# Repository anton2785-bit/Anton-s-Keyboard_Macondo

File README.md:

# Anton's kayboard
--- 
### What is this project
* This is a keyboar that uses thr 1800 compact layout (an almost 100% keyboard without most of the keys between the enter and the numpad). This keyboard uses an rp2040 chip for its 30 gpio pins that make the making of the keyboard PCB layout easier. Bellow every hotswapable key there is a LED that is wired to every other one and can be controlled with code. 

--- 
### Why I made this project
* I made this keyboard because I wanted to try a bigger more complx PCB that I would be able to use everyday.
* Also I wanted to update my keyboard with one that I made.

--- 
### Images
* The schematic for the PCB

* The schematic for the hierarchal sheets and what is in it

* The layout and the PCB

* The 3D model of the case and assembly of the keyboard
* 

--- 
### BOM
| Component | Purpose | Qty | Total Cost (USD) | Distributor |
|-----------|---------|:---:|:----------------:|-------------|
| Gateron Stabilizer | Prevents larger switches from wobbling | 1 | $9.45 | Gateron |
| Decoupling Capacitors (100nF) | Reduce electrical noise before the LEDs | 2 | $3.20 | AliExpress |
| LEDs (SK6812 Mini-E) | RGB underglow beneath the switches | 1 | $3.56 | AliExpress |
| Keycaps | Keycaps | 1 | $15.78 | AliExpress |
| Rotary Encoder (EC11E) | Rotary knob for volume / scroll | 1 | $2.78 | AliExpress |
| Diodes (1N4148W) | Prevent signal backflow in the matrix | 2 | $3.60 | AliExpress |
| Resistors (4.7 kΩ and 350 Ω) | Current limiting for LEDs and I²C pull-ups | 1 | $4.10 | AliExpress |
| Foam | Sound dampening layer under the PCB | 1 | $7.77 | AliExpress |
| Coiled Cable | Connecting cable for the keyboard | 1 | $5.55 | AliExpress |
| PCB | Main circuit board | 1 | $59.00 | JLCPCB |
| Microcontroller (YD-RP2040) | Runs the keyboard firmware (KMK / CircuitPython) | 1 | $2.94 | AliExpress |
| Gateron Switches | The switches you type on | 1 | $29.00 | Gateron |
| Hotswap Sockets | Allow switches to be swapped without soldering | 1 | $6.68 | Gateron |
| **Total** | | | **$153.51** | |

--- 
### Assembly
* First you need to soulder the smaller components (the diodes and capacitors) just for your sanity because later it will get harder.
* The secpnd smallest thingyou need to soulder many of are the LEDs.
* After that you are free to soulder the hotswap sockets.
* The chip can be souldered at any time.
* The keys and kaycaps must be placed after the PCB is put into the case and secured with the top case.

--- 
### Known problems
* The code is almost entirely made by claude because I dont have the chip with me and I cant write the code.

--- 
### Credits
* Designed and built by *(Anton/ Anton-2785-bit)
* Inspired by open‑source mechanical keyboard and hackpad communities (https://forge.hackclub.com/).

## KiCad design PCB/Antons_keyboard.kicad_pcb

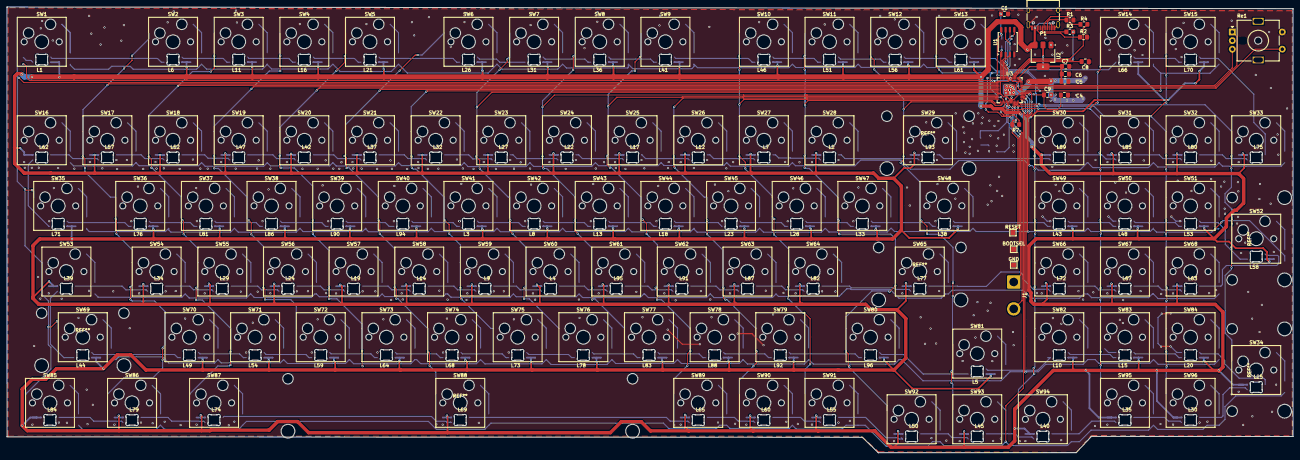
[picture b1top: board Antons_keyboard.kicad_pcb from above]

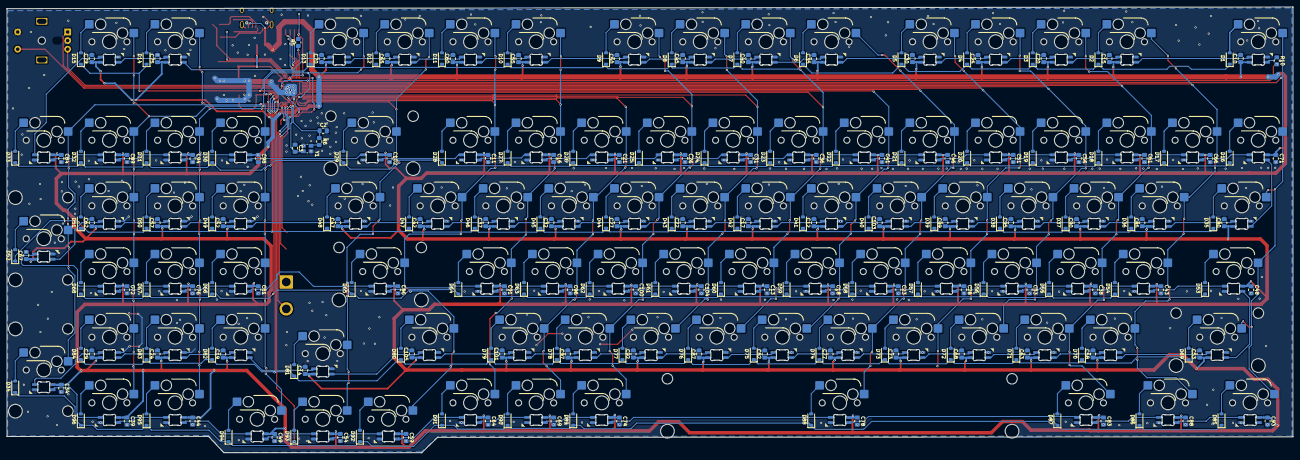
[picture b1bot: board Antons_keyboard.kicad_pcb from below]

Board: 2 copper layers, 373.2 x 129.3 mm, 411 parts (198 on the bottom side), 241 nets.

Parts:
BOOTSEL: TestPoint; TestPoint_Pad_1.5x1.5mm
C1, C4, C5, C6, C7, C9: 100nF; C_0805_2012Metric_Pad1.18x1.45mm_HandSolder
C2, C3: 27pF; C_0805_2012Metric_Pad1.18x1.45mm_HandSolder
C8: 1uF; C_0805_2012Metric_Pad1.18x1.45mm_HandSolder
C10, C11, C12, C13, C14, C15, C16, C17, C18, C19, C20, C21, C22, C23, C24, C25, C26, C27, C28, C29, C30, C31, C32, C33, C34, C35, C36, C37, C38, C39, C40, C41, C42, C43, C44, C45, C46, C47, C48, C49, C50, C51, C52, C53, C54, C55, C56, C57, C58, C59, C60, C61, C62, C63, C64, C65, C66, C67, C68, C69, C70, C71, C72, C73, C74, C75, C76, C77, C78, C79, C80, C81, C82, C83, C84, C85, C86, C87, C88, C89, C90, C91, C92, C93, C94, C95, C96, C97, C98, C99, C100, C101, C102, C103, C104, C105: C; C_0805_2012Metric_Pad1.18x1.45mm_HandSolder
D1, D2, D3, D4, D5, D6, D7, D8, D9, D10, D11, D12, D13, D14, D15, D16, D17, D18, D19, D20, D21, D22, D23, D24, D25, D26, D27, D28, D29, D30, D31, D32, D33, D34, D35, D36, D37, D38, D39, D40, D41, D42, D43, D44, D45, D46, D47, D48, D49, D50, D51, D52, D53, D54, D55, D56, D57, D58, D59, D60, D61, D62, D63, D64, D65, D66, D67, D68, D69, D70, D71, D72, D73, D74, D75, D76, D77, D78, D79, D80, D81, D82, D83, D84, D85, D86, D87, D88, D89, D90, D91, D92, D93, D94, D95, D96: 1N4148W; D_SOD-123
GND: TestPoint; TestPoint_Pad_1.5x1.5mm
J1: debug pins; SolderWire-2sqmm_1x02_P7.8mm_D2mm_OD3.9mm
L1, L2, L3, L4, L5, L6, L7, L8, L9, L10, L11, L12, L13, L14, L15, L16, L17, L18, L19, L20, L21, L22, L23, L24, L25, L26, L27, L28, L29, L30, L31, L32, L33, L34, L35, L36, L37, L38, L39, L40, L41, L42, L43, L44, L45, L46, L47, L48, L49, L50, L51, L52, L53, L54, L55, L56, L57, L58, L59, L60, L61, L62, L63, L64, L65, L66, L67, L68, L69, L70, L71, L72, L73, L74, L75, L76, L77, L78, L79, L80, L81, L82, L83, L84, L85, L86, L87, L88, L89, L90, L91, L92, L93, L94, L95, L96: SK6812MINI-E; SK6812MINI-E_fixed
P1: USB_C_Plug_USB2.0; USB_C_Receptacle_HRO_TYPE-C-31-M-12
R1, R2: 5.1kΩ; R_0805_2012Metric_Pad1.20x1.40mm_HandSolder
R3, R4: 27Ω; R_0805_2012Metric_Pad1.20x1.40mm_HandSolder
R5, R7: 10k; R_0805_2012Metric_Pad1.20x1.40mm_HandSolder
R6: 1k; R_0805_2012Metric_Pad1.20x1.40mm_HandSolder
R10: 470; R_0805_2012Metric_Pad1.20x1.40mm_HandSolder
RESET: TestPoint; TestPoint_Pad_1.5x1.5mm
Re1: RotaryEncoder_Switch; RotaryEncoder_Alps_EC11E-Switch_Vertical_H20mm_MountingHoles
SW1, SW2, SW3, SW4, SW5, SW6, SW7, SW8, SW9, SW10, SW11, SW12, SW13, SW14, SW15, SW16, SW17, SW18, SW19, SW20, SW21, SW22, SW23, SW24, SW25, SW26, SW27, SW28, SW30, SW31, SW32, SW33, SW36, SW37, SW38, SW39, SW40, SW41, SW42, SW43, SW44, SW45, SW46, SW47, SW49, SW50, SW51, SW54, SW55, SW56, SW57, SW58, SW59, SW60, SW61, SW62, SW63, SW64, SW66, SW67, SW68, SW70, SW71, SW72, SW73, SW74, SW75, SW76, SW77, SW78, SW79, SW80, SW81, SW82, SW83, SW84, SW89, SW90, SW91, SW92, SW93, SW94, SW95, SW96: SW_Push; Hotswap_MX_1.00u
SW29: SW_Push; Hotswap_MX_2.00u
SW34, SW52: SW_Push; Hotswap_MX_2.00u_90deg
SW35, SW48: SW_Push; Hotswap_MX_1.50u
SW53: SW_Push; Hotswap_MX_1.75u
SW65, SW69: SW_Push; Hotswap_MX_2.25u
SW85, SW86, SW87: SW_Push; Hotswap_MX_1.25u
SW88: SW_Push; Hotswap_MX_6.25u
U1: W25Q32JVSS; SOIC-8_5.3x5.3mm_P1.27mm
U2: AMS1117-3.3; SOT-223-3_TabPin2
U3: RP2040; QFN-56-1EP_7x7mm_P0.4mm_EP3.2x3.2mm
Y1: TSX-3225_12.0000MF18X-C; XTAL_TSX-3225_24.0000MF18X-C

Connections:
+3.3V: C1.1, C4.1, C5.1, C6.1, C7.1, C9.1, R5.2, R7.1, U1.8 (VCC), U2.2 (VO), U3.1 (IOVDD), U3.10 (IOVDD), U3.22 (IOVDD), U3.23 (DVDD), U3.33 (IOVDD), U3.42 (IOVDD), U3.43 (ADC_AVDD), U3.44 (VREG_VIN), U3.48 (USB_VDD), U3.49 (IOVDD), U3.50 (DVDD)
+5V: C10.1, C11.1, C12.1, C13.1, C14.1, C15.1, C16.1, C17.1, C18.1, C19.1, C20.1, C21.1, C22.1, C23.1, C24.1, C25.1, C26.1, C27.1, C28.1, C29.1, C30.1, C31.1, C32.1, C33.1, C34.1, C35.1, C36.1, C37.1, C38.1, C39.1, C40.1, C41.1, C42.1, C43.1, C44.1, C45.1, C46.1, C47.1, C48.1, C49.1, C50.1, C51.1, C52.1, C53.1, C54.1, C55.1, C56.1, C57.1, C58.1, C59.1, C60.1, C61.1, C62.1, C63.1, C64.1, C65.1, C66.1, C67.1, C68.1, C69.1, C70.1, C71.1, C72.1, C73.1, C74.1, C75.1, C76.1, C77.1, C78.1, C79.1, C80.1, C81.1, C82.1, C83.1, C84.1, C85.1, C86.1, C87.1, C88.1, C89.1, C90.1, C91.1, C92.1, C93.1, C94.1, C95.1, C96.1, C97.1, C98.1, C99.1, C100.1, C101.1, C102.1, C103.1, C104.1, C105.1, L1.1 (VDD), L2.1 (VDD), L3.1 (VDD), L4.1 (VDD), L5.1 (VDD), L6.1 (VDD), L7.1 (VDD), L8.1 (VDD), L9.1 (VDD), L10.1 (VDD), L11.1 (VDD), L12.1 (VDD), L13.1 (VDD), L14.1 (VDD), L15.1 (VDD), L16.1 (VDD), L17.1 (VDD), L18.1 (VDD), L19.1 (VDD), L20.1 (VDD), L21.1 (VDD), L22.1 (VDD), L23.1 (VDD), L24.1 (VDD), L25.1 (VDD), L26.1 (VDD), L27.1 (VDD), L28.1 (VDD), L29.1 (VDD), L30.1 (VDD), L31.1 (VDD), L32.1 (VDD), L33.1 (VDD), L34.1 (VDD), L35.1 (VDD), L36.1 (VDD), L37.1 (VDD), L38.1 (VDD), L39.1 (VDD), L40.1 (VDD), L41.1 (VDD), L42.1 (VDD), L43.1 (VDD), L44.1 (VDD), L45.1 (VDD), L46.1 (VDD), L47.1 (VDD), L48.1 (VDD), L49.1 (VDD), L50.1 (VDD), L51.1 (VDD), L52.1 (VDD), L53.1 (VDD), L54.1 (VDD), L55.1 (VDD), L56.1 (VDD), L57.1 (VDD), L58.1 (VDD), L59.1 (VDD), L60.1 (VDD), L61.1 (VDD), L62.1 (VDD), L63.1 (VDD), L64.1 (VDD), L65.1 (VDD), L66.1 (VDD), L67.1 (VDD), L68.1 (VDD), L69.1 (VDD), L70.1 (VDD), L71.1 (VDD), L72.1 (VDD), L73.1 (VDD), L74.1 (VDD), L75.1 (VDD), L76.1 (VDD), L77.1 (VDD), L78.1 (VDD), L79.1 (VDD), L80.1 (VDD), L81.1 (VDD), L82.1 (VDD), L83.1 (VDD), L84.1 (VDD), L85.1 (VDD), L86.1 (VDD), L87.1 (VDD), L88.1 (VDD), L89.1 (VDD), L90.1 (VDD), L91.1 (VDD), L92.1 (VDD), L93.1 (VDD), L94.1 (VDD), L95.1 (VDD), L96.1 (VDD), P1.A4 (VBUS), P1.A9 (VBUS), P1.B4 (VBUS), P1.B9 (VBUS), U2.3 (VI)
DATA LED: R10.2, U3.36 (GPIO24)
GND: C1.2, C2.2, C3.1, C4.2, C5.2, C6.2, C7.2, C8.1, C9.2, C10.2, C11.2, C12.2, C13.2, C14.2, C15.2, C16.2, C17.2, C18.2, C19.2, C20.2, C21.2, C22.2, C23.2, C24.2, C25.2, C26.2, C27.2, C28.2, C29.2, C30.2, C31.2, C32.2, C33.2, C34.2, C35.2, C36.2, C37.2, C38.2, C39.2, C40.2, C41.2, C42.2, C43.2, C44.2, C45.2, C46.2, C47.2, C48.2, C49.2, C50.2, C51.2, C52.2, C53.2, C54.2, C55.2, C56.2, C57.2, C58.2, C59.2, C60.2, C61.2, C62.2, C63.2, C64.2, C65.2, C66.2, C67.2, C68.2, C69.2, C70.2, C71.2, C72.2, C73.2, C74.2, C75.2, C76.2, C77.2, C78.2, C79.2, C80.2, C81.2, C82.2, C83.2, C84.2, C85.2, C86.2, C87.2, C88.2, C89.2, C90.2, C91.2, C92.2, C93.2, C94.2, C95.2, C96.2, C97.2, C98.2, C99.2, C100.2, C101.2, C102.2, C103.2, C104.2, C105.2, GND.1 (1_1), L1.3 (VSS), L2.3 (VSS), L3.3 (VSS), L4.3 (VSS), L5.3 (VSS), L6.3 (VSS), L7.3 (VSS), L8.3 (VSS), L9.3 (VSS), L10.3 (VSS), L11.3 (VSS), L12.3 (VSS), L13.3 (VSS), L14.3 (VSS), L15.3 (VSS), L16.3 (VSS), L17.3 (VSS), L18.3 (VSS), L19.3 (VSS), L20.3 (VSS), L21.3 (VSS), L22.3 (VSS), L23.3 (VSS), L24.3 (VSS), L25.3 (VSS), L26.3 (VSS), L27.3 (VSS), L28.3 (VSS), L29.3 (VSS), L30.3 (VSS), L31.3 (VSS), L32.3 (VSS), L33.3 (VSS), L34.3 (VSS), L35.3 (VSS), L36.3 (VSS), L37.3 (VSS), L38.3 (VSS), L39.3 (VSS), L40.3 (VSS), L41.3 (VSS), L42.3 (VSS), L43.3 (VSS), L44.3 (VSS), L45.3 (VSS), L46.3 (VSS), L47.3 (VSS), L48.3 (VSS), L49.3 (VSS), L50.3 (VSS), L51.3 (VSS), L52.3 (VSS), L53.3 (VSS), L54.3 (VSS), L55.3 (VSS), L56.3 (VSS), L57.3 (VSS), L58.3 (VSS), L59.3 (VSS), L60.3 (VSS), L61.3 (VSS), L62.3 (VSS), L63.3 (VSS), L64.3 (VSS), L65.3 (VSS), L66.3 (VSS), L67.3 (VSS), L68.3 (VSS), L69.3 (VSS), L70.3 (VSS), L71.3 (VSS), L72.3 (VSS), L73.3 (VSS), L74.3 (VSS), L75.3 (VSS), L76.3 (VSS), L77.3 (VSS), L78.3 (VSS), L79.3 (VSS), L80.3 (VSS), L81.3 (VSS), L82.3 (VSS), L83.3 (VSS), L84.3 (VSS), L85.3 (VSS), L86.3 (VSS), L87.3 (VSS), L88.3 (VSS), L89.3 (VSS), L90.3 (VSS), L91.3 (VSS), L92.3 (VSS), L93.3 (VSS), L94.3 (VSS), L95.3 (VSS), L96.3 (VSS), P1.A1 (GND), P1.A12 (GND), P1.B1 (GND), P1.B12 (GND), P1.SH (SHIELD), R1.2, R2.2, Re1.C, Re1.S2, U1.4 (GND), U2.1 (GND), U3.19 (TESTEN), U3.57 (GND), Y1.2 (GND), Y1.4 (GND)
unnamed: D1.2 (A), SW1.2
unnamed: D2.2 (A), SW2.2
unnamed: D3.2 (A), SW3.2
unnamed: D4.2 (A), SW4.2
unnamed: D5.2 (A), SW5.2
unnamed: D6.2 (A), SW6.2
unnamed: D7.2 (A), SW7.2
unnamed: D8.2 (A), SW8.2
unnamed: D9.2 (A), SW9.2
unnamed: D10.2 (A), SW10.2
unnamed: D11.2 (A), SW11.2
unnamed: D12.2 (A), SW12.2
unnamed: D13.2 (A), SW13.2
unnamed: D14.2 (A), SW14.2
unnamed: D15.2 (A), SW15.2
unnamed: D16.2 (A), SW16.2
unnamed: D17.2 (A), SW17.2
unnamed: D18.2 (A), SW18.2
unnamed: D19.2 (A), SW19.2
unnamed: D20.2 (A), SW20.2
unnamed: D21.2 (A), SW21.2
unnamed: D22.2 (A), SW22.2
unnamed: D23.2 (A), SW23.2
unnamed: D24.2 (A), SW24.2
unnamed: D25.2 (A), SW25.2
unnamed: D26.2 (A), SW26.2
unnamed: D27.2 (A), SW27.2
unnamed: D28.2 (A), SW28.2
unnamed: D29.2 (A), SW29.2
unnamed: D30.2 (A), SW30.2
unnamed: D31.2 (A), SW31.2
unnamed: D32.2 (A), SW32.2
unnamed: D33.2 (A), SW33.2
unnamed: D34.2 (A), SW34.2
unnamed: D35.2 (A), SW35.2
unnamed: D36.2 (A), SW36.2
unnamed: D37.2 (A), SW37.2
unnamed: D38.2 (A), SW38.2
unnamed: D39.2 (A), SW39.2
unnamed: D40.2 (A), SW40.2
unnamed: D41.2 (A), SW41.2
unnamed: D42.2 (A), SW42.2
unnamed: D43.2 (A), SW43.2
unnamed: D44.2 (A), SW44.2
unnamed: D45.2 (A), SW45.2
unnamed: D46.2 (A), SW46.2
unnamed: D47.2 (A), SW47.2
unnamed: D48.2 (A), SW48.2
unnamed: D49.2 (A), SW49.2
unnamed: D50.2 (A), SW50.2
unnamed: D51.2 (A), SW51.2
unnamed: D52.2 (A), SW52.2
unnamed: D53.2 (A), SW53.2
unnamed: D54.2 (A), SW54.2
unnamed: D55.2 (A), SW55.2
unnamed: D56.2 (A), SW56.2
unnamed: D57.2 (A), SW57.2
unnamed: D58.2 (A), SW58.2
unnamed: D59.2 (A), SW59.2
unnamed: D60.2 (A), SW60.2
unnamed: D61.2 (A), SW61.2
unnamed: D62.2 (A), SW62.2
unnamed: D63.2 (A), SW63.2
unnamed: D64.2 (A), SW64.2
unnamed: D65.2 (A), SW65.2
unnamed: D66.2 (A), SW66.2
unnamed: D67.2 (A), SW67.2
unnamed: D68.2 (A), SW68.2
unnamed: D69.2 (A), SW69.2
unnamed: D70.2 (A), SW70.2
unnamed: D71.2 (A), SW71.2
unnamed: D72.2 (A), SW72.2
unnamed: D73.2 (A), SW73.2
unnamed: D74.2 (A), SW74.2
unnamed: D75.2 (A), SW75.2
unnamed: D76.2 (A), SW76.2
unnamed: D77.2 (A), SW77.2
unnamed: D78.2 (A), SW78.2
unnamed: D79.2 (A), SW79.2
unnamed: D80.2 (A), SW80.2
unnamed: D81.2 (A), SW81.2
unnamed: D82.2 (A), SW82.2
unnamed: D83.2 (A), SW83.2
unnamed: D84.2 (A), SW84.2
unnamed: D85.2 (A), SW85.2
unnamed: D86.2 (A), SW86.2
unnamed: D87.2 (A), SW87.2
unnamed: D88.2 (A), SW88.2
unnamed: D89.2 (A), SW89.2
unnamed: D90.2 (A), SW90.2
unnamed: D91.2 (A), SW91.2
unnamed: D92.2 (A), SW92.2
unnamed: D93.2 (A), SW93.2
unnamed: D94.2 (A), SW94.2
unnamed: D95.2 (A), SW95.2
unnamed: D96.2 (A), SW96.2
unnamed: J1.1, U3.24 (SWCLK)
unnamed: J1.2, U3.25 (SWDIO)
unnamed: L1.4 (DIN), R10.1
unnamed: L1.2 (DOUT), L6.4 (DIN)
unnamed: L2.4 (DIN), L93.2 (DOUT)
unnamed: L2.2 (DOUT), L7.4 (DIN)
unnamed: L3.4 (DIN), L94.2 (DOUT)
unnamed: L3.2 (DOUT), L8.4 (DIN)
unnamed: L4.4 (DIN), L95.2 (DOUT)
unnamed: L4.2 (DOUT), L9.4 (DIN)
unnamed: L5.4 (DIN), L96.2 (DOUT)
unnamed: L5.2 (DOUT), L10.4 (DIN)
unnamed: L10.2 (DOUT), L15.4 (DIN)
unnamed: L6.2 (DOUT), L11.4 (DIN)
unnamed: L11.2 (DOUT), L16.4 (DIN)
unnamed: L7.2 (DOUT), L12.4 (DIN)
unnamed: L12.2 (DOUT), L17.4 (DIN)
unnamed: L8.2 (DOUT), L13.4 (DIN)
unnamed: L13.2 (DOUT), L18.4 (DIN)
unnamed: L9.2 (DOUT), L14.4 (DIN)
unnamed: L14.2 (DOUT), L19.4 (DIN)
unnamed: L15.2 (DOUT), L20.4 (DIN)
unnamed: L16.2 (DOUT), L21.4 (DIN)
unnamed: L17.2 (DOUT), L22.4 (DIN)
unnamed: L18.2 (DOUT), L23.4 (DIN)
unnamed: L19.2 (DOUT), L24.4 (DIN)
unnamed: L20.2 (DOUT), L25.4 (DIN)
unnamed: L21.2 (DOUT), L26.4 (DIN)
unnamed: L22.2 (DOUT), L27.4 (DIN)
unnamed: L23.2 (DOUT), L28.4 (DIN)
unnamed: L24.2 (DOUT), L29.4 (DIN)
unnamed: L25.2 (DOUT), L30.4 (DIN)
unnamed: L26.2 (DOUT), L31.4 (DIN)
unnamed: L27.2 (DOUT), L32.4 (DIN)
unnamed: L28.2 (DOUT), L33.4 (DIN)
unnamed: L29.2 (DOUT), L34.4 (DIN)
unnamed: L30.2 (DOUT), L35.4 (DIN)
unnamed: L31.2 (DOUT), L36.4 (DIN)
unnamed: L32.2 (DOUT), L37.4 (DIN)
unnamed: L33.2 (DOUT), L38.4 (DIN)
unnamed: L34.2 (DOUT), L39.4 (DIN)
unnamed: L35.2 (DOUT), L40.4 (DIN)
unnamed: L36.2 (DOUT), L41.4 (DIN)
unnamed: L37.2 (DOUT), L42.4 (DIN)
unnamed: L38.2 (DOUT), L43.4 (DIN)
unnamed: L39.2 (DOUT), L44.4 (DIN)
unnamed: L40.2 (DOUT), L45.2 (DOUT), L45.4 (DIN), L50.4 (DIN)
unnamed: L41.2 (DOUT), L46.4 (DIN)
unnamed: L42.2 (DOUT), L47.4 (DIN)
unnamed: L43.2 (DOUT), L48.4 (DIN)
unnamed: L44.2 (DOUT), L49.4 (DIN)
unnamed: L46.2 (DOUT), L51.4 (DIN)
unnamed: L47.2 (DOUT), L52.4 (DIN)
unnamed: L48.2 (DOUT), L53.4 (DIN)
unnamed: L49.2 (DOUT), L54.4 (DIN)
unnamed: L50.2 (DOUT), L55.4 (DIN)
unnamed: L51.2 (DOUT), L56.4 (DIN)
unnamed: L52.2 (DOUT), L57.4 (DIN)
unnamed: L53.2 (DOUT), L58.4 (DIN)
unnamed: L54.2 (DOUT), L59.4 (DIN)
unnamed: L55.2 (DOUT), L60.4 (DIN)
unnamed: L56.2 (DOUT), L61.4 (DIN)
unnamed: L57.2 (DOUT), L62.4 (DIN)
unnamed: L58.2 (DOUT), L63.4 (DIN)
unnamed: L59.2 (DOUT), L64.4 (DIN)
unnamed: L60.2 (DOUT), L65.4 (DIN)
unnamed: L61.2 (DOUT), L66.4 (DIN)
unnamed: L62.2 (DOUT), L71.4 (DIN)
unnamed: L63.2 (DOUT), L67.4 (DIN)
unnamed: L64.2 (DOUT), L68.4 (DIN)
unnamed: L65.2 (DOUT), L69.4 (DIN)
unnamed: L66.2 (DOUT), L70.4 (DIN)
unnamed: L67.2 (DOUT), L72.4 (DIN)
unnamed: L68.2 (DOUT), L73.4 (DIN)
unnamed: L69.2 (DOUT), L74.4 (DIN)
unnamed: L70.2 (DOUT), L75.4 (DIN)
unnamed: L71.2 (DOUT), L76.4 (DIN)
unnamed: L72.2 (DOUT), L77.4 (DIN)
unnamed: L73.2 (DOUT), L78.4 (DIN)
unnamed: L74.2 (DOUT), L79.4 (DIN)
unnamed: L75.2 (DOUT), L80.4 (DIN)
unnamed: L76.2 (DOUT), L81.4 (DIN)
unnamed: L77.2 (DOUT), L82.4 (DIN)
unnamed: L78.2 (DOUT), L83.4 (DIN)
unnamed: L79.2 (DOUT), L84.4 (DIN)
unnamed: L80.2 (DOUT), L85.4 (DIN)
unnamed: L81.2 (DOUT), L86.4 (DIN)
unnamed: L82.2 (DOUT), L87.4 (DIN)
unnamed: L83.2 (DOUT), L88.4 (DIN)
unnamed: L85.2 (DOUT), L89.4 (DIN)
unnamed: L86.2 (DOUT), L90.4 (DIN)
unnamed: L87.2 (DOUT), L91.4 (DIN)
unnamed: L88.2 (DOUT), L92.4 (DIN)
unnamed: L89.2 (DOUT), L93.4 (DIN)
unnamed: L90.2 (DOUT), L94.4 (DIN)
unnamed: L91.2 (DOUT), L95.4 (DIN)
unnamed: L92.2 (DOUT), L96.4 (DIN)
unnamed: P1.A5 (CC), R1.1
unnamed: P1.A6 (D+), R4.1
unnamed: P1.A7 (D-), R3.1
unnamed: P1.B5 (VCONN), R2.1
unnamed: R6.2, Y1.1
unnamed: U1.6 (CLK), U3.52 (QSPI_SCLK)
unnamed: U1.5 (DI/IO_{0}), U3.53 (QSPI_SD0)
unnamed: U1.2 (DO/IO_{1}), U3.55 (QSPI_SD1)
unnamed: BOOTSEL.1 (1_1), R5.1, U1.1 (~CS), U3.56 (~QSPI_SS)
unnamed: U1.7 (~HOLD/~RESET/IO_{3}), U3.51 (QSPI_SD3)
unnamed: U1.3 (~WP/IO_{2}), U3.54 (QSPI_SD2)
unnamed: Re1.S1, U3.37 (GPIO25)
unnamed: Re1.A, U3.38 (GPIO26/ADC0)
unnamed: Re1.B, U3.39 (GPIO27/ADC1)
unnamed: R7.2, RESET.1 (1_1), U3.26 (RUN)
unnamed: R3.2, U3.46 (USB_DM)
unnamed: R4.2, U3.47 (USB_DP)
unnamed: C8.2, U3.45 (VREG_VOUT)
unnamed: C2.1, R6.1, U3.20 (XIN)
unnamed: C3.2, U3.21 (XOUT), Y1.3
column 1: SW1.1, SW16.1, SW35.1, SW53.1, SW69.1, SW85.1, U3.2 (GPIO0)
column 2: SW2.1, SW17.1, SW36.1, SW54.1, SW70.1, SW86.1, U3.3 (GPIO1)
column 3: SW3.1, SW18.1, SW37.1, SW55.1, SW71.1, SW87.1, U3.4 (GPIO2)
column 4: SW4.1, SW19.1, SW38.1, SW56.1, SW72.1, U3.5 (GPIO3)
column 5: SW5.1, SW20.1, SW39.1, SW57.1, SW73.1, U3.6 (GPIO4)
column 6: SW6.1, SW21.1, SW40.1, SW58.1, SW74.1, SW88.1, U3.7 (GPIO5)
column 7: SW22.1, SW41.1, SW59.1, SW75.1, U3.8 (GPIO6)
column 8: SW7.1, SW23.1, SW42.1, SW60.1, SW76.1, U3.9 (GPIO7)
column 9: SW8.1, SW24.1, SW43.1, SW61.1, SW77.1, U3.11 (GPIO8)
column 10: SW9.1, SW25.1, SW44.1, SW62.1, SW78.1, SW89.1, U3.12 (GPIO9)
column 11: SW26.1, SW45.1, SW63.1, SW79.1, SW90.1, U3.13 (GPIO10)
column 12: SW10.1, SW27.1, SW46.1, SW64.1, SW91.1, U3.14 (GPIO11)
column 13: SW11.1, SW28.1, SW47.1, SW65.1, SW80.1, SW92.1, U3.15 (GPIO12)
column 14: SW12.1, SW29.1, SW48.1, SW81.1, SW93.1, U3.16 (GPIO13)
column 15: SW13.1, SW30.1, SW49.1, SW66.1, SW82.1, SW94.1, U3.17 (GPIO14)
column 16: SW14.1, SW31.1, SW50.1, SW67.1, SW83.1, SW95.1, U3.18 (GPIO15)
column 17: SW15.1, SW32.1, SW51.1, SW68.1, SW84.1, SW96.1, U3.27 (GPIO16)
column 18: SW33.1, SW34.1, SW52.1, U3.28 (GPIO17)
row 1: D1.1 (K), D2.1 (K), D3.1 (K), D4.1 (K), D5.1 (K), D6.1 (K), D7.1 (K), D8.1 (K), D9.1 (K), D10.1 (K), D11.1 (K), D12.1 (K), D13.1 (K), D14.1 (K), D15.1 (K), U3.35 (GPIO23)
row 2: D16.1 (K), D17.1 (K), D18.1 (K), D19.1 (K), D20.1 (K), D21.1 (K), D22.1 (K), D23.1 (K), D24.1 (K), D25.1 (K), D26.1 (K), D27.1 (K), D28.1 (K), D29.1 (K), D30.1 (K), D31.1 (K), D32.1 (K), D33.1 (K), U3.34 (GPIO22)
row 3: D35.1 (K), D36.1 (K), D37.1 (K), D38.1 (K), D39.1 (K), D40.1 (K), D41.1 (K), D42.1 (K), D43.1 (K), D44.1 (K), D45.1 (K), D46.1 (K), D47.1 (K), D48.1 (K), D49.1 (K), D50.1 (K), D51.1 (K), D52.1 (K), U3.32 (GPIO21)
row 4: D53.1 (K), D54.1 (K), D55.1 (K), D56.1 (K), D57.1 (K), D58.1 (K), D59.1 (K), D60.1 (K), D61.1 (K), D62.1 (K), D63.1 (K), D64.1 (K), D65.1 (K), D66.1 (K), D67.1 (K), D68.1 (K), U3.31 (GPIO20)
row 5: D69.1 (K), D70.1 (K), D71.1 (K), D72.1 (K), D73.1 (K), D74.1 (K), D75.1 (K), D76.1 (K), D77.1 (K), D78.1 (K), D79.1 (K), D80.1 (K), D81.1 (K), D82.1 (K), D83.1 (K), D84.1 (K), U3.30 (GPIO19)
row 6: D34.1 (K), D85.1 (K), D86.1 (K), D87.1 (K), D88.1 (K), D89.1 (K), D90.1 (K), D91.1 (K), D92.1 (K), D93.1 (K), D94.1 (K), D95.1 (K), D96.1 (K), U3.29 (GPIO18)

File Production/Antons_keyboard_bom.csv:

Designator,Footprint,Quantity,Value,LCSC Part #
"BOOTSEL, GND, RESET",TestPoint_Pad_1.5x1.5mm,3,TestPoint,
"C1, C4, C5, C6, C7, C9",0805,6,100nF,
"C10, C100, C101, C102, C103, C104, C105, C11, C12, C13, C14, C15, C16, C17, C18, C19, C20, C21, C22, C23, C24, C25, C26, C27, C28, C29, C30, C31, C32, C33, C34, C35, C36, C37, C38, C39, C40, C41, C42, C43, C44, C45, C46, C47, C48, C49, C50, C51, C52, C53, C54, C55, C56, C57, C58, C59, C60, C61, C62, C63, C64, C65, C66, C67, C68, C69, C70, C71, C72, C73, C74, C75, C76, C77, C78, C79, C80, C81, C82, C83, C84, C85, C86, C87, C88, C89, C90, C91, C92, C93, C94, C95, C96, C97, C98, C99",0805,96,C,
"C2, C3",0805,2,27pF,
C8,0805,1,1uF,
"D1, D10, D11, D12, D13, D14, D15, D16, D17, D18, D19, D2, D20, D21, D22, D23, D24, D25, D26, D27, D28, D29, D3, D30, D31, D32, D33, D34, D35, D36, D37, D38, D39, D4, D40, D41, D42, D43, D44, D45, D46, D47, D48, D49, D5, D50, D51, D52, D53, D54, D55, D56, D57, D58, D59, D6, D60, D61, D62, D63, D64, D65, D66, D67, D68, D69, D7, D70, D71, D72, D73, D74, D75, D76, D77, D78, D79, D8, D80, D81, D82, D83, D84, D85, D86, D87, D88, D89, D9, D90, D91, D92, D93, D94, D95, D96",D_SOD-123,96,1N4148W,
J1,SolderWire-2sqmm_1x02_P7.8mm_D2mm_OD3.9mm,1,debug pins,
"L1, L10, L11, L12, L13, L14, L15, L16, L17, L18, L19, L2, L20, L21, L22, L23, L24, L25, L26, L27, L28, L29, L3, L30, L31, L32, L33, L34, L35, L36, L37, L38, L39, L4, L40, L41, L42, L43, L44, L45, L46, L47, L48, L49, L5, L50, L51, L52, L53, L54, L55, L56, L57, L58, L59, L6, L60, L61, L62, L63, L64, L65, L66, L67, L68, L69, L7, L70, L71, L72, L73, L74, L75, L76, L77, L78, L79, L8, L80, L81, L82, L83, L84, L85, L86, L87, L88, L89, L9, L90, L91, L92, L93, L94, L95, L96",SK6812MINI-E_fixed,96,SK6812MINI-E,
P1,USB_C_Receptacle_HRO_TYPE-C-31-M-12,1,USB_C_Plug_USB2.0,
"R1, R2",0805,2,5.1kΩ,
R10,0805,1,470,
"R3, R4",0805,2,27Ω,
"R5, R7",0805,2,10k,
R6,0805,1,1k,
RE1,RotaryEncoder_Alps_EC11E-Switch_Vertical_H20mm_MountingHoles,1,RotaryEncoder_Switch,
"SW1, SW10, SW11, SW12, SW13, SW14, SW15, SW16, SW17, SW18, SW19, SW2, SW20, SW21, SW22, SW23, SW24, SW25, SW26, SW27, SW28, SW3, SW30, SW31, SW32, SW33, SW36, SW37, SW38, SW39, SW4, SW40, SW41, SW42, SW43, SW44, SW45, SW46, SW47, SW49, SW5, SW50, SW51, SW54, SW55, SW56, SW57, SW58, SW59, SW6, SW60, SW61, SW62, SW63, SW64, SW66, SW67, SW68, SW7, SW70, SW71, SW72, SW73, SW74, SW75, SW76, SW77, SW78, SW79, SW8, SW80, SW81, SW82, SW83, SW84, SW89, SW9, SW90, SW91, SW92, SW93, SW94, SW95, SW96",Hotswap_MX_1.00u,84,SW_Push,
SW29,Hotswap_MX_2.00u,1,SW_Push,
"SW34, SW52",Hotswap_MX_2.00u_90deg,2,SW_Push,
"SW35, SW48",Hotswap_MX_1.50u,2,SW_Push,
SW53,Hotswap_MX_1.75u,1,SW_Push,
"SW65, SW69",Hotswap_MX_2.25u,2,SW_Push,
"SW85, SW86, SW87",Hotswap_MX_1.25u,3,SW_Push,
SW88,Hotswap_MX_6.25u,1,SW_Push,
U1,SOIC-8_5.3x5.3mm_P1.27mm,1,W25Q32JVSS,
U2,SOT-223-3_TabPin2,1,AMS1117-3.3,
U3,QFN-56-1EP_7x7mm_P0.4mm_EP3.2x3.2mm,1,RP2040,
Y1,XTAL_TSX-3225_24.0000MF18X-C,1,TSX-3225_12.0000MF18X-C,

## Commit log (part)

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2026-06-19 File update
